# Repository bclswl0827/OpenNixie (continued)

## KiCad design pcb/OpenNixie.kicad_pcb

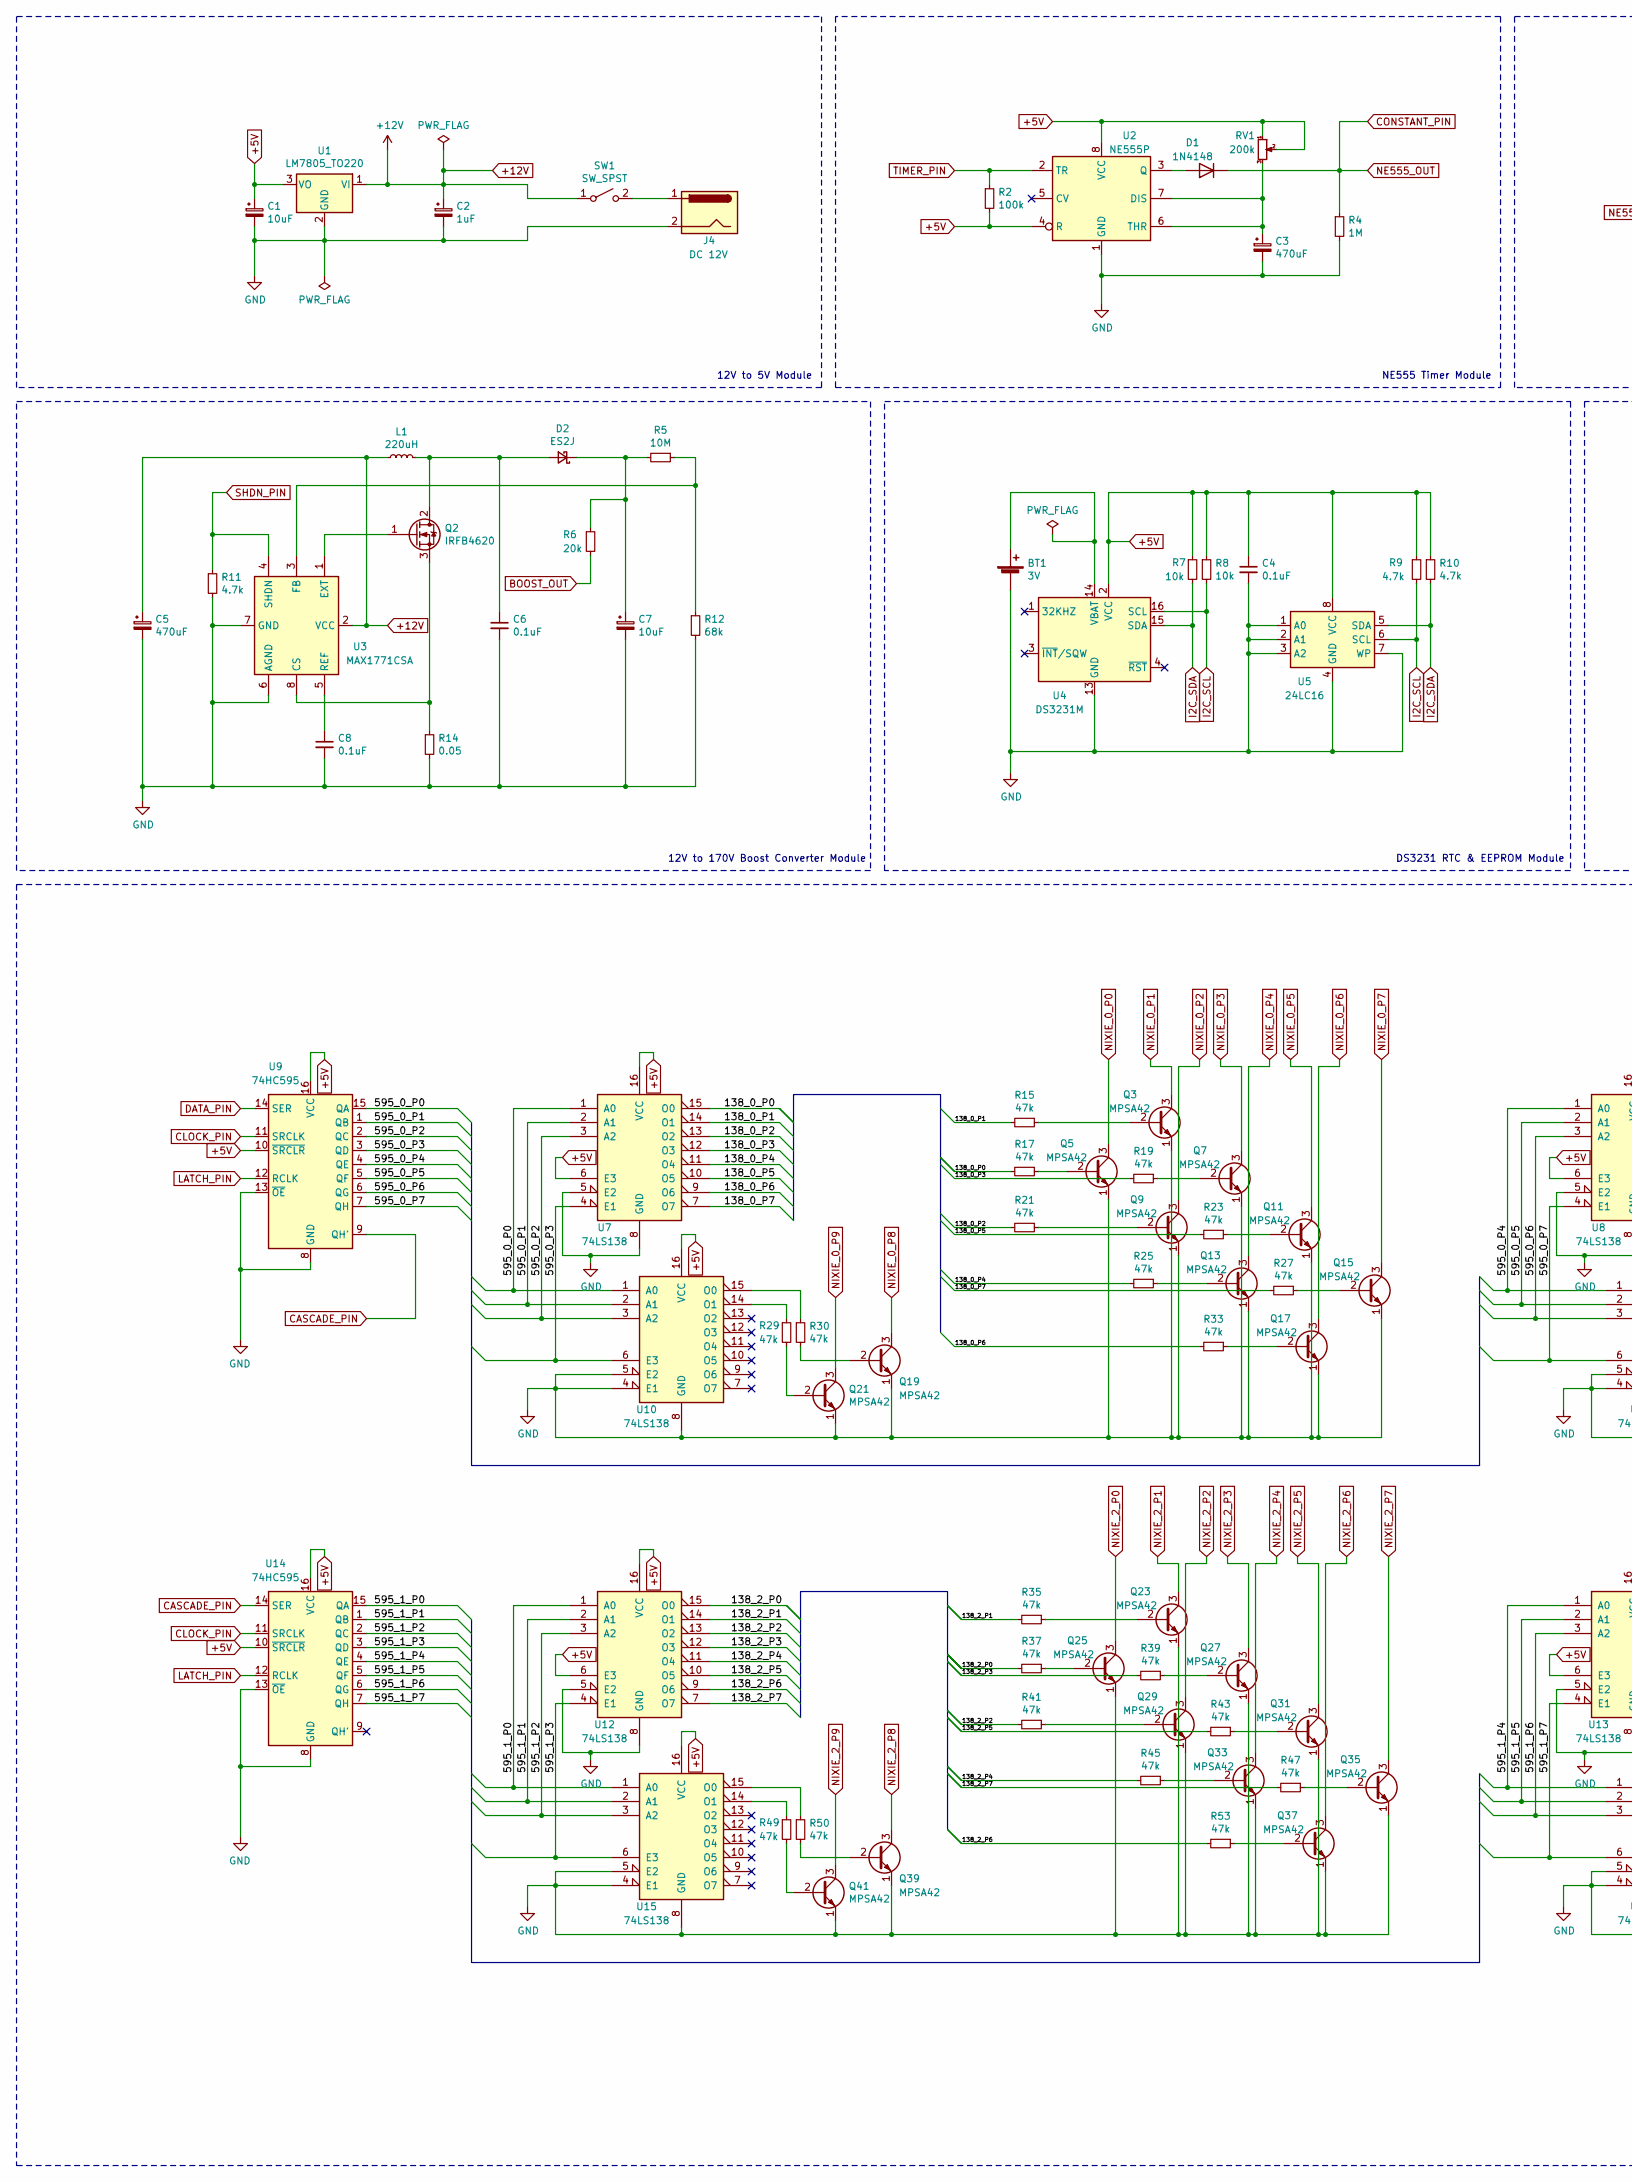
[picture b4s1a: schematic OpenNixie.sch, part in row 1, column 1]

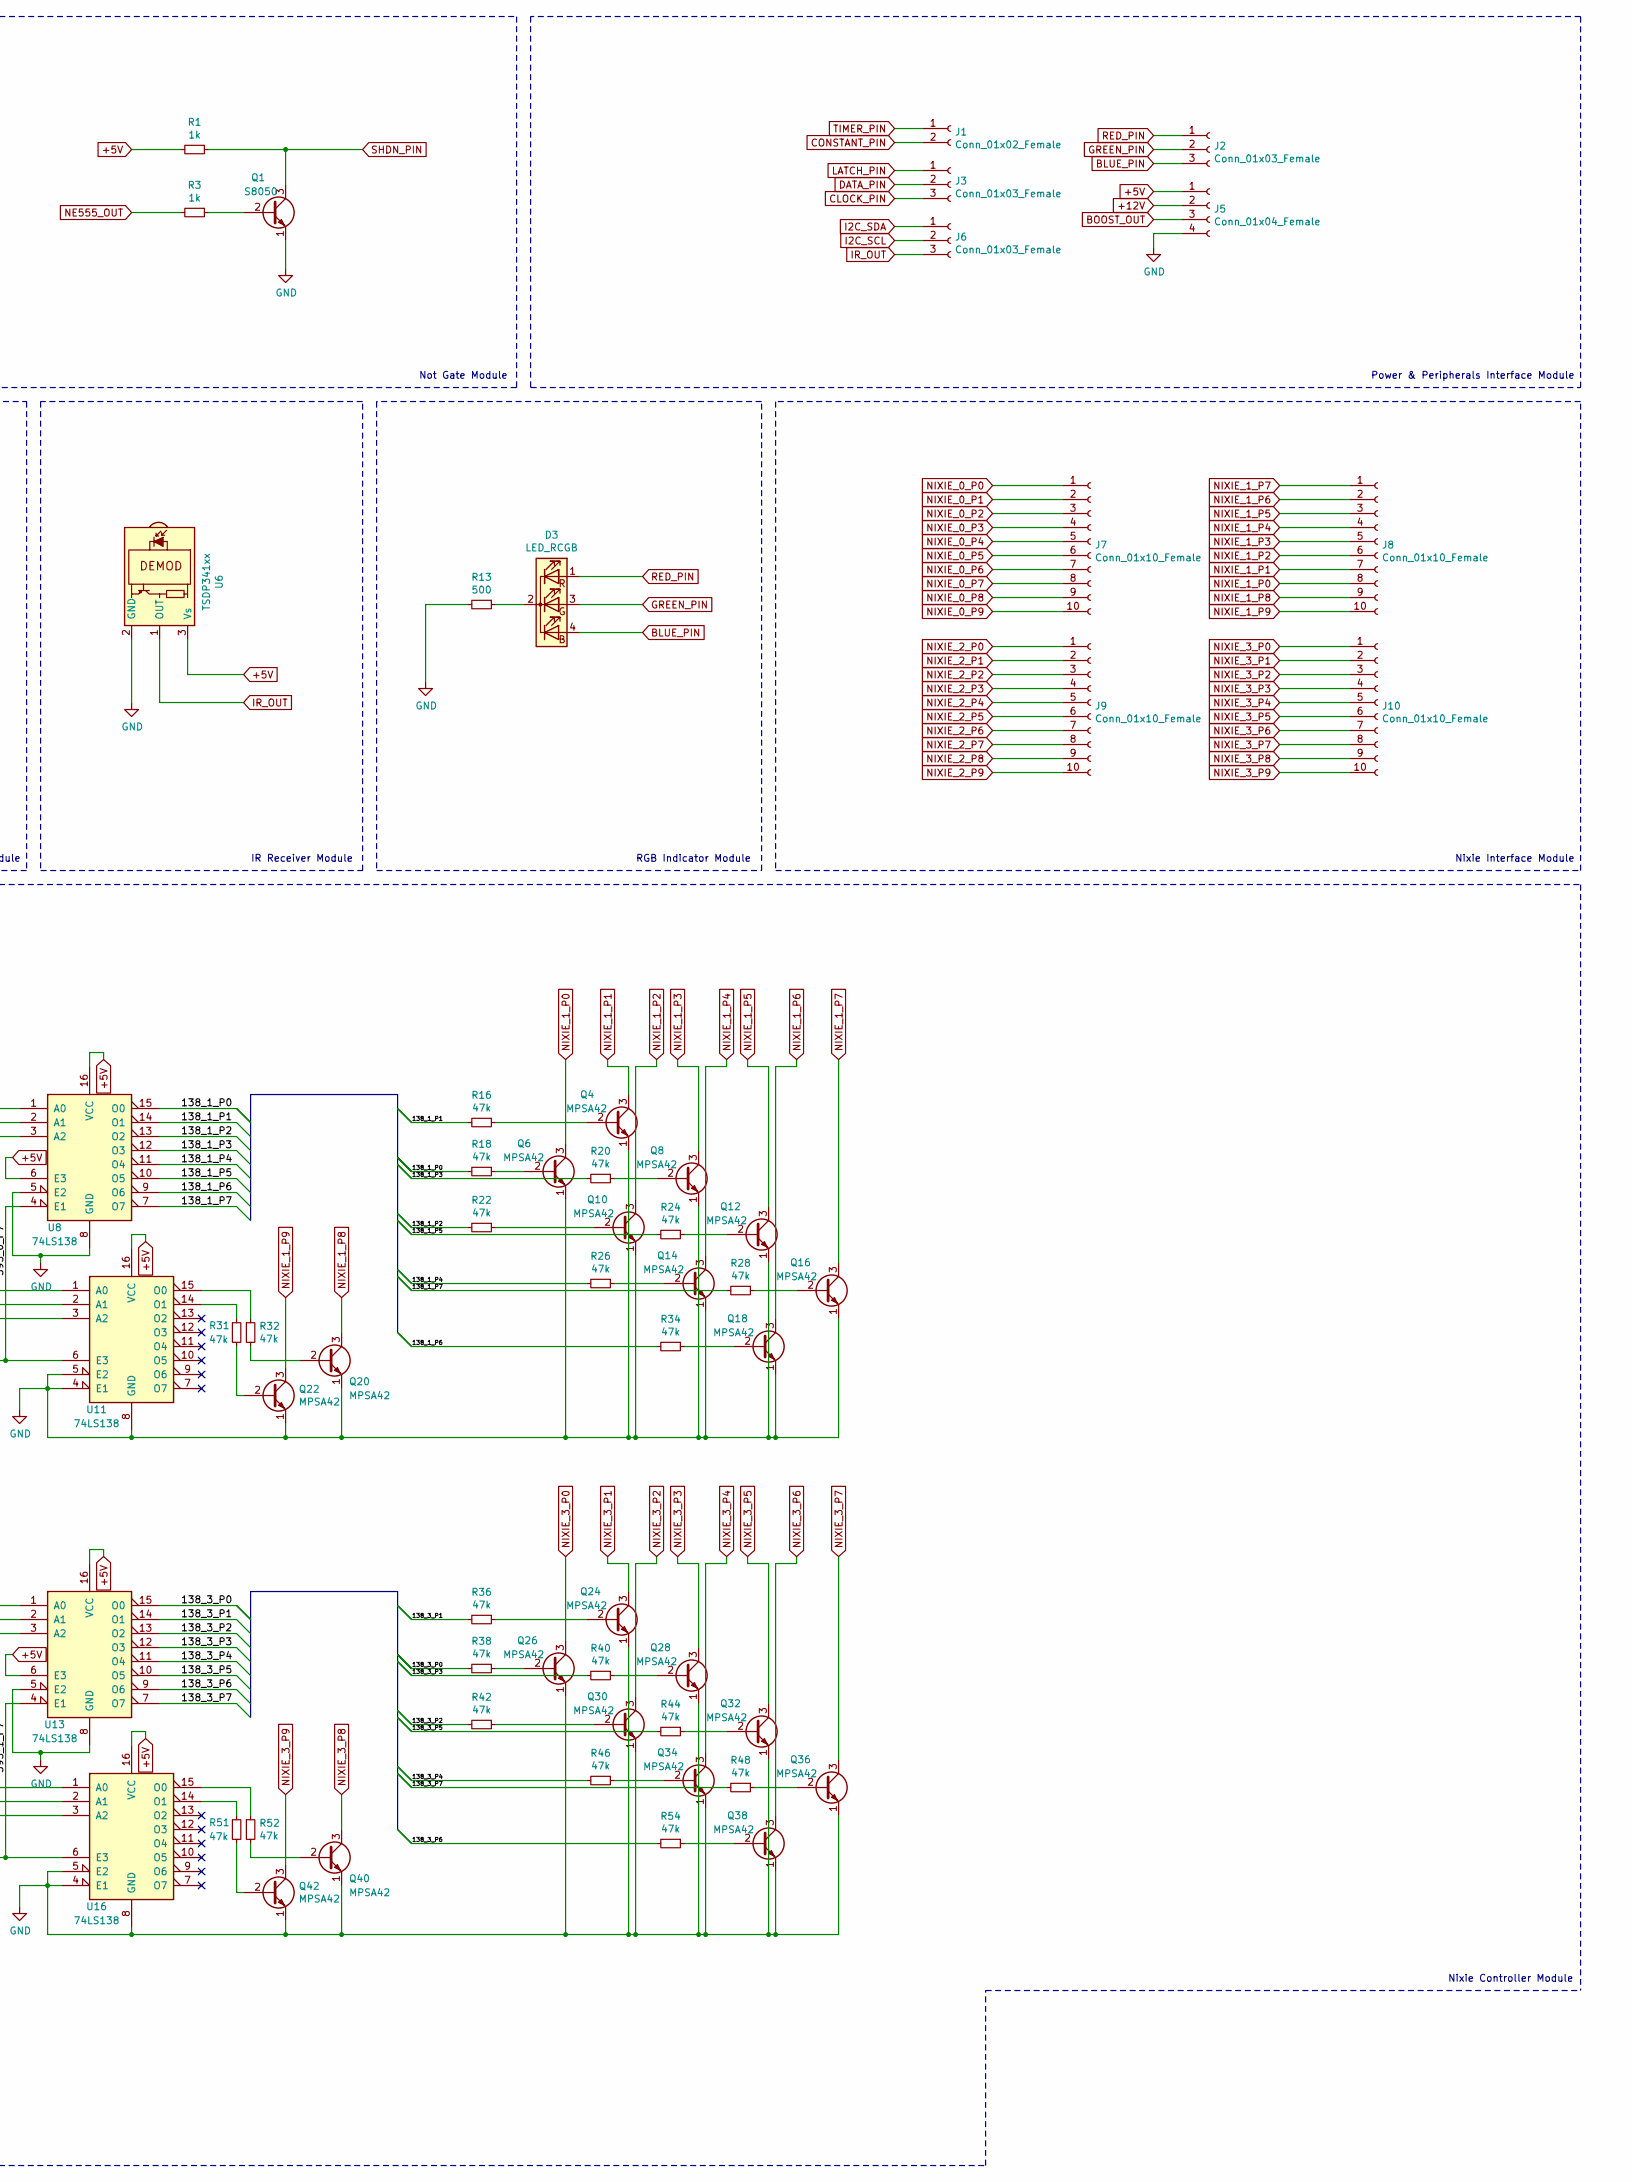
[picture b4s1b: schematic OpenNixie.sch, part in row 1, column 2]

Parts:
BT1: 3V; BatteryHolder_Keystone_1058_1x2032
C1, C7: 10uF; CP_Radial_D5.0mm_P2.50mm
C2: 1uF; CP_Radial_D5.0mm_P2.50mm
C3, C5: 470uF; CP_Radial_D8.0mm_P3.50mm
C4, C8: 0.1uF; C_Disc_D3.0mm_W2.0mm_P2.50mm
C6: 0.1uF; C_Disc_D3.0mm_W1.6mm_P2.50mm
D1: 1N4148; D_DO-35_SOD27_P7.62mm_Horizontal
D2: ES2J; D_SMA
D3: LED_RCGB; LED_D5.0mm-4_RGB
J1: Conn_01x02_Female; PinSocket_1x02_P2.54mm_Vertical
J2, J3, J6: Conn_01x03_Female; PinSocket_1x03_P2.54mm_Vertical
J4: DC 12V; BarrelJack_Horizontal
J5: Conn_01x04_Female; PinSocket_1x04_P2.54mm_Vertical
J7, J8, J9, J10: Conn_01x10_Female; PinSocket_1x10_P2.54mm_Vertical
L1: 220uH; L_Radial_D7.0mm_P3.00mm
Q1: S8050; TO-92_Inline
Q2: IRFB4620; TO-220-3_Horizontal_TabDown
Q3, Q4, Q5, Q6, Q7, Q8, Q9, Q10, Q11, Q12, Q13, Q14, Q15, Q16, Q17, Q18, Q19, Q20, Q21, Q22, Q23, Q24, Q25, Q26, Q27, Q28, Q29, Q30, Q31, Q32, Q33, Q34, Q35, Q36, Q37, Q38, Q39, Q40, Q41, Q42: MPSA42; TO-92_Inline
R1, R3: 1k; R_Axial_DIN0204_L3.6mm_D1.6mm_P7.62mm_Horizontal
R2: 100k; R_Axial_DIN0204_L3.6mm_D1.6mm_P7.62mm_Horizontal
R4: 1M; R_Axial_DIN0204_L3.6mm_D1.6mm_P7.62mm_Horizontal
R5: 10M; R_Axial_DIN0204_L3.6mm_D1.6mm_P7.62mm_Horizontal
R6: 20k; R_Axial_DIN0204_L3.6mm_D1.6mm_P7.62mm_Horizontal
R7, R8: 10k; R_Axial_DIN0204_L3.6mm_D1.6mm_P7.62mm_Horizontal
R9, R10, R11: 4.7k; R_Axial_DIN0204_L3.6mm_D1.6mm_P7.62mm_Horizontal
R12: 68k; R_Axial_DIN0204_L3.6mm_D1.6mm_P7.62mm_Horizontal
R13: 500; R_Axial_DIN0204_L3.6mm_D1.6mm_P7.62mm_Horizontal
R14: 0.05; R_Axial_DIN0207_L6.3mm_D2.5mm_P10.16mm_Horizontal
R15, R16, R17, R18, R19, R20, R21, R22, R23, R24, R25, R26, R27, R28, R29, R30, R31, R32, R33, R34, R35, R36, R37, R38, R39, R40, R41, R42, R43, R44, R45, R46, R47, R48, R49, R50, R51, R52, R53, R54: 47k; R_Axial_DIN0204_L3.6mm_D1.6mm_P7.62mm_Horizontal
RV1: 200k; Potentiometer_Vishay_T73YP_Vertical
SW1: SW_SPST; SW_DIP_SPSTx01_Slide_9.78x4.72mm_W7.62mm_P2.54mm
U1: LM7805_TO220; TO-220-3_Vertical
U2: NE555P; DIP-8_W7.62mm
U3: MAX1771CSA; SOIC-8-1EP_3.9x4.9mm_P1.27mm_EP2.29x3mm
U4: DS3231M; SOIC-16W_7.5x10.3mm_P1.27mm
U5: 24LC16; DIP-8_W7.62mm
U6: TSDP341xx; Vishay_MOLD-3Pin
U7, U8, U10, U11, U12, U13, U15, U16: 74LS138; DIP-16_W7.62mm
U9, U14: 74HC595; DIP-16_W7.62mm

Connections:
+5V: C1.1, C4.1, J5.1, R1.2, R2.2, R7.1, R8.1, R9.1, R10.1, RV1.1, RV1.2, U1.3 (VO), U2.4 (R), U2.8 (VCC), U4.2 (VCC), U5.8 (VCC), U6.3 (Vs), U7.6 (E3), U7.16 (VCC), U8.6 (E3), U8.16 (VCC), U9.10 (~SRCLR), U9.16 (VCC), U10.16 (VCC), U11.16 (VCC), U12.6 (E3), U12.16 (VCC), U13.6 (E3), U13.16 (VCC), U14.10 (~SRCLR), U14.16 (VCC), U15.16 (VCC), U16.16 (VCC)
+12V: C2.1, C5.1, J5.2, L1.1, SW1.1 (A), U1.1 (VI), U3.2 (VCC)
/138_0_P0: R17.2, U7.15 (O0)
/138_0_P1: R15.2, U7.14 (O1)
/138_0_P2: R21.2, U7.13 (O2)
/138_0_P3: R19.2, U7.12 (O3)
/138_0_P4: R25.2, U7.11 (O4)
/138_0_P5: R23.2, U7.10 (O5)
/138_0_P6: R33.2, U7.9 (O6)
/138_0_P7: R27.2, U7.7 (O7)
/138_1_P0: R18.2, U8.15 (O0)
/138_1_P1: R16.2, U8.14 (O1)
/138_1_P2: R22.2, U8.13 (O2)
/138_1_P3: R20.2, U8.12 (O3)
/138_1_P4: R26.2, U8.11 (O4)
/138_1_P5: R24.2, U8.10 (O5)
/138_1_P6: R34.2, U8.9 (O6)
/138_1_P7: R28.2, U8.7 (O7)
/138_2_P0: R37.2, U12.15 (O0)
/138_2_P1: R35.2, U12.14 (O1)
/138_2_P2: R41.2, U12.13 (O2)
/138_2_P3: R39.2, U12.12 (O3)
/138_2_P4: R45.2, U12.11 (O4)
/138_2_P5: R43.2, U12.10 (O5)
/138_2_P6: R53.2, U12.9 (O6)
/138_2_P7: R47.2, U12.7 (O7)
/138_3_P0: R38.2, U13.15 (O0)
/138_3_P1: R36.2, U13.14 (O1)
/138_3_P2: R42.2, U13.13 (O2)
/138_3_P3: R40.2, U13.12 (O3)
/138_3_P4: R46.2, U13.11 (O4)
/138_3_P5: R44.2, U13.10 (O5)
/138_3_P6: R54.2, U13.9 (O6)
/138_3_P7: R48.2, U13.7 (O7)
/595_0_P0: U7.1 (A0), U9.15 (QA), U10.1 (A0)
/595_0_P1: U7.2 (A1), U9.1 (QB), U10.2 (A1)
/595_0_P2: U7.3 (A2), U9.2 (QC), U10.3 (A2)
/595_0_P3: U7.4 (E1), U9.3 (QD), U10.6 (E3)
/595_0_P4: U8.1 (A0), U9.4 (QE), U11.1 (A0)
/595_0_P5: U8.2 (A1), U9.5 (QF), U11.2 (A1)
/595_0_P6: U8.3 (A2), U9.6 (QG), U11.3 (A2)
/595_0_P7: U8.4 (E1), U9.7 (QH), U11.6 (E3)
/595_1_P0: U12.1 (A0), U14.15 (QA), U15.1 (A0)
/595_1_P1: U12.2 (A1), U14.1 (QB), U15.2 (A1)
/595_1_P2: U12.3 (A2), U14.2 (QC), U15.3 (A2)
/595_1_P3: U12.4 (E1), U14.3 (QD), U15.6 (E3)
/595_1_P4: U13.1 (A0), U14.4 (QE), U16.1 (A0)
/595_1_P5: U13.2 (A1), U14.5 (QF), U16.2 (A1)
/595_1_P6: U13.3 (A2), U14.6 (QG), U16.3 (A2)
/595_1_P7: U13.4 (E1), U14.7 (QH), U16.6 (E3)
BLUE_PIN: D3.4 (BA), J2.3
BOOST_OUT: J5.3, R6.2
CASCADE_PIN: U9.9 (QH'), U14.14 (SER)
CLOCK_PIN: J3.3, U9.11 (SRCLK), U14.11 (SRCLK)
CONSTANT_PIN: D1.1 (K), J1.2, R3.2, R4.1
DATA_PIN: J3.2, U9.14 (SER)
GND: BT1.2 (-), C1.2, C2.2, C3.2, C4.2, C5.2, C6.2, C7.2, C8.2, J4.2, J5.4, Q1.1 (E), Q3.1 (E), Q4.1 (E), Q5.1 (E), Q6.1 (E), Q7.1 (E), Q8.1 (E), Q9.1 (E), Q10.1 (E), Q11.1 (E), Q12.1 (E), Q13.1 (E), Q14.1 (E), Q15.1 (E), Q16.1 (E), Q17.1 (E), Q18.1 (E), Q19.1 (E), Q20.1 (E), Q21.1 (E), Q22.1 (E), Q23.1 (E), Q24.1 (E), Q25.1 (E), Q26.1 (E), Q27.1 (E), Q28.1 (E), Q29.1 (E), Q30.1 (E), Q31.1 (E), Q32.1 (E), Q33.1 (E), Q34.1 (E), Q35.1 (E), Q36.1 (E), Q37.1 (E), Q38.1 (E), Q39.1 (E), Q40.1 (E), Q41.1 (E), Q42.1 (E), R4.2, R11.2, R12.2, R13.2, R14.2, U1.2 (GND), U2.1 (GND), U3.6 (AGND), U3.7 (GND), U4.5 (GND), U4.6 (GND), U4.7 (GND), U4.8 (GND), U4.9 (GND), U4.10 (GND), U4.11 (GND), U4.12 (GND), U4.13 (GND), U5.1 (A0), U5.2 (A1), U5.3 (A2), U5.4 (GND), U5.7 (WP), U6.2 (GND), U7.5 (E2), U7.8 (GND), U8.5 (E2), U8.8 (GND), U9.8 (GND), U9.13 (~OE), U10.4 (E1), U10.5 (E2), U10.8 (GND), U11.4 (E1), U11.5 (E2), U11.8 (GND), U12.5 (E2), U12.8 (GND), U13.5 (E2), U13.8 (GND), U14.8 (GND), U14.13 (~OE), U15.4 (E1), U15.5 (E2), U15.8 (GND), U16.4 (E1), U16.5 (E2), U16.8 (GND)
GREEN_PIN: D3.3 (GA), J2.2
I2C_SCL: J6.2, R8.2, R9.2, U4.16 (SCL), U5.6 (SCL)
I2C_SDA: J6.1, R7.2, R10.2, U4.15 (SDA), U5.5 (SDA)
IR_OUT: J6.3, U6.1 (OUT)
LATCH_PIN: J3.1, U9.12 (RCLK), U14.12 (RCLK)
NIXIE_0_P0: J7.1, Q5.3 (C)
NIXIE_0_P1: J7.2, Q3.3 (C)
NIXIE_0_P2: J7.3, Q9.3 (C)
NIXIE_0_P3: J7.4, Q7.3 (C)
NIXIE_0_P4: J7.5, Q13.3 (C)
NIXIE_0_P5: J7.6, Q11.3 (C)
NIXIE_0_P6: J7.7, Q17.3 (C)
NIXIE_0_P7: J7.8, Q15.3 (C)
NIXIE_0_P8: J7.9, Q19.3 (C)
NIXIE_0_P9: J7.10, Q21.3 (C)
NIXIE_1_P0: J8.8, Q6.3 (C)
NIXIE_1_P1: J8.7, Q4.3 (C)
NIXIE_1_P2: J8.6, Q10.3 (C)
NIXIE_1_P3: J8.5, Q8.3 (C)
NIXIE_1_P4: J8.4, Q14.3 (C)
NIXIE_1_P5: J8.3, Q12.3 (C)
NIXIE_1_P6: J8.2, Q18.3 (C)
NIXIE_1_P7: J8.1, Q16.3 (C)
NIXIE_1_P8: J8.9, Q20.3 (C)
NIXIE_1_P9: J8.10, Q22.3 (C)
NIXIE_2_P0: J9.1, Q25.3 (C)
NIXIE_2_P1: J9.2, Q23.3 (C)
NIXIE_2_P2: J9.3, Q29.3 (C)
NIXIE_2_P3: J9.4, Q27.3 (C)
NIXIE_2_P4: J9.5, Q33.3 (C)
NIXIE_2_P5: J9.6, Q31.3 (C)
NIXIE_2_P6: J9.7, Q37.3 (C)
NIXIE_2_P7: J9.8, Q35.3 (C)
NIXIE_2_P8: J9.9, Q39.3 (C)
NIXIE_2_P9: J9.10, Q41.3 (C)
NIXIE_3_P0: J10.1, Q26.3 (C)
NIXIE_3_P1: J10.2, Q24.3 (C)
NIXIE_3_P2: J10.3, Q30.3 (C)
NIXIE_3_P3: J10.4, Q28.3 (C)
NIXIE_3_P4: J10.5, Q34.3 (C)
NIXIE_3_P5: J10.6, Q32.3 (C)
NIXIE_3_P6: J10.7, Q38.3 (C)
NIXIE_3_P7: J10.8, Q36.3 (C)
NIXIE_3_P8: J10.9, Q40.3 (C)
NIXIE_3_P9: J10.10, Q42.3 (C)
unnamed: BT1.1 (+), U4.14 (VBAT)
unnamed: C3.1, RV1.3, U2.6 (THR), U2.7 (DIS)
unnamed: C6.1, D2.2 (A), L1.2, Q2.2 (D)
unnamed: C7.1, D2.1 (K), R5.2, R6.1
unnamed: C8.1, U3.5 (REF)
unnamed: D1.2 (A), U2.3 (Q)
unnamed: D3.2 (K), R13.1
unnamed: J4.1, SW1.2 (B)
unnamed: Q1.2 (B), R3.1
unnamed: Q2.1 (G), U3.1 (EXT)
unnamed: Q2.3 (S), R14.1, U3.8 (CS)
unnamed: Q3.2 (B), R15.1
unnamed: Q4.2 (B), R16.1
unnamed: Q5.2 (B), R17.1
unnamed: Q6.2 (B), R18.1
unnamed: Q7.2 (B), R19.1
unnamed: Q8.2 (B), R20.1
unnamed: Q9.2 (B), R21.1
unnamed: Q10.2 (B), R22.1
unnamed: Q11.2 (B), R23.1
unnamed: Q12.2 (B), R24.1
unnamed: Q13.2 (B), R25.1
unnamed: Q14.2 (B), R26.1
unnamed: Q15.2 (B), R27.1
unnamed: Q16.2 (B), R28.1
unnamed: Q17.2 (B), R33.1
unnamed: Q18.2 (B), R34.1
unnamed: Q19.2 (B), R30.2
unnamed: Q20.2 (B), R32.2
unnamed: Q21.2 (B), R29.2
unnamed: Q22.2 (B), R31.2
unnamed: Q23.2 (B), R35.1
unnamed: Q24.2 (B), R36.1
unnamed: Q25.2 (B), R37.1
unnamed: Q26.2 (B), R38.1
unnamed: Q27.2 (B), R39.1
unnamed: Q28.2 (B), R40.1
unnamed: Q29.2 (B), R41.1
unnamed: Q30.2 (B), R42.1
unnamed: Q31.2 (B), R43.1
unnamed: Q32.2 (B), R44.1
unnamed: Q33.2 (B), R45.1
unnamed: Q34.2 (B), R46.1
unnamed: Q35.2 (B), R47.1
unnamed: Q36.2 (B), R48.1
unnamed: Q37.2 (B), R53.1
unnamed: Q38.2 (B), R54.1
unnamed: Q39.2 (B), R50.2
unnamed: Q40.2 (B), R52.2
unnamed: Q41.2 (B), R49.2
unnamed: Q42.2 (B), R51.2
unnamed: R5.1, R12.1, U3.3 (FB)
unnamed: R29.1, U10.14 (O1)
unnamed: R30.1, U10.15 (O0)
unnamed: R31.1, U11.14 (O1)
unnamed: R32.1, U11.15 (O0)
unnamed: R49.1, U15.14 (O1)
unnamed: R50.1, U15.15 (O0)
unnamed: R51.1, U16.14 (O1)
unnamed: R52.1, U16.15 (O0)
RED_PIN: D3.1 (RA), J2.1
SHDN_PIN: Q1.3 (C), R1.1, R11.1, U3.4 (SHDN)
TIMER_PIN: J1.1, R2.1, U2.2 (TR)

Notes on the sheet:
NE555 Timer Module
Not Gate Module
DS3231 RTC & EEPROM Module
RGB Indicator Module
IR Receiver Module
12V to 170V Boost Converter Module
Power & Peripherals Interface Module
Nixie Interface Module
Nixie Controller Module
12V to 5V Module

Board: 2 copper layers, 137 parts (0 on the bottom side), 165 nets, no tracks yet.

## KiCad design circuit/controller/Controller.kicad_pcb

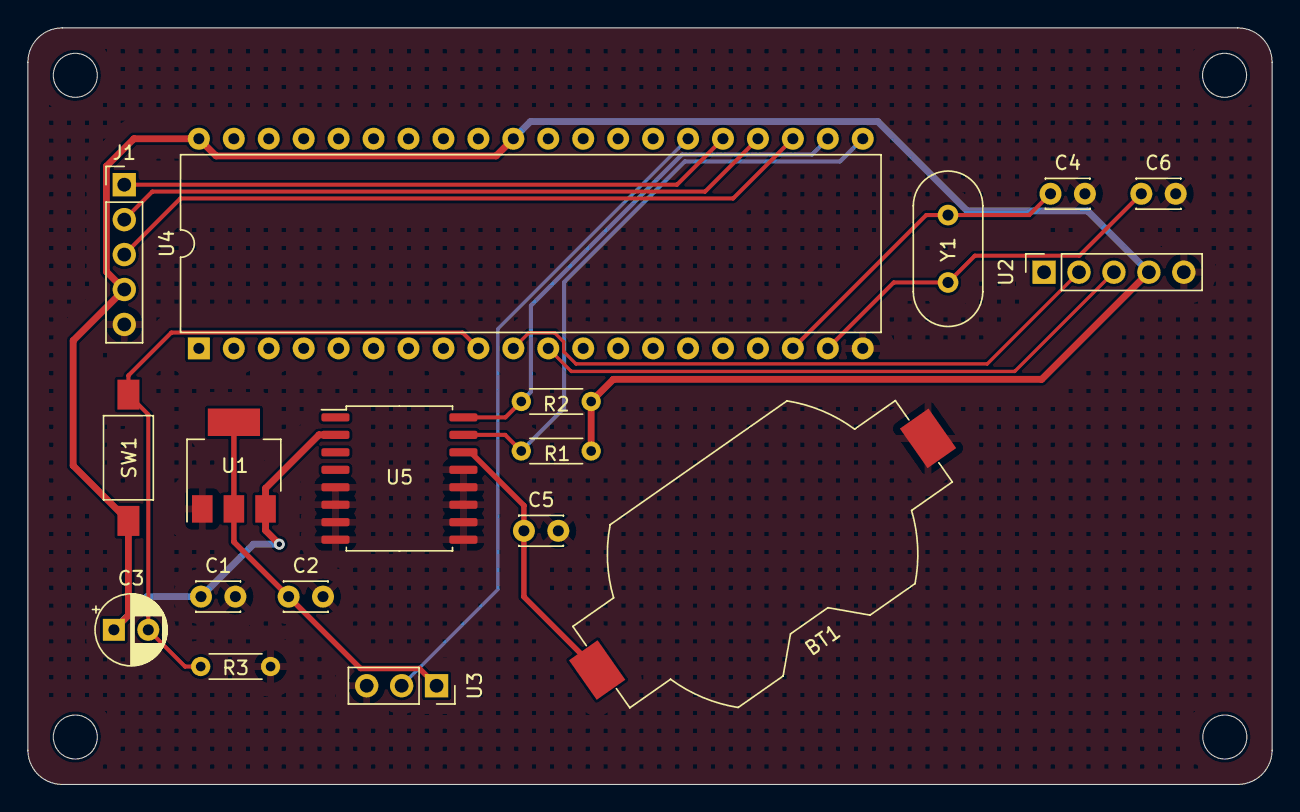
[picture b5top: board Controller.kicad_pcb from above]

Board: 2 copper layers, 90.5 x 55.0 mm, 22 parts (0 on the bottom side), 15 nets.

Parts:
BT1: 3V; BatteryHolder_Keystone_1058_1x2032
C1, C2, C5: 0.1uF; C_Disc_D3.0mm_W2.0mm_P2.50mm
C3: 10uF; CP_Radial_D5.0mm_P2.50mm
C4, C6: 20pF; C_Disc_D3.0mm_W2.0mm_P2.50mm
H1, H2, H3, H4: MountingHole; MountingHole_3.2mm_M3
J1: Conn_01x05; PinHeader_1x05_P2.54mm_Vertical
R1, R2, R3: 10k; R_Axial_DIN0204_L3.6mm_D1.6mm_P5.08mm_Horizontal
SW1: SW_Push; SW_SPST_FSMSM
U1: AMS1117-3.3; SOT-223-3_TabPin2
U2: JDY-34; PinSocket_1x05_P2.54mm_Vertical
U3: AM312; PinSocket_1x03_P2.54mm_Vertical
U4: AT89C52; DIP-40_W15.24mm
U5: DS3231M; SOIC-16W_7.5x10.3mm_P1.27mm
Y1: 11.0592MHz; Crystal_HC18-U_Vertical

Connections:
+5V: C1.1, C3.1, J1.4, R1.2, R2.2, SW1.1, U1.3 (VI), U2.4 (VCC), U4.31 (~EA/VPP), U4.40 (VCC), U5.2 (VCC)
/+3.3V: C2.1, U1.2 (VO), U3.1 (VCC)
/BLE_RXD: U2.3 (RXD), U4.11 (P3.1(TXD))
/BLE_TXD: U2.2 (TXD), U4.10 (P3.0(RXD))
/I2C_SCL: R2.1, U4.22 (P2.1), U5.16 (SCL)
/I2C_SDA: R1.1, U4.21 (P2.0), U5.15 (SDA)
/PIR: U3.2 (OUT), U4.26 (P2.5)
/SR_CLK: J1.3, U4.23 (P2.2)
/SR_DAT: J1.2, U4.24 (P2.3)
/SR_LCH: J1.1, U4.25 (P2.4)
/VBAT: BT1.1 (+), C5.1, U5.14 (VBAT)
GND: BT1.2 (-), C1.2, C2.2, C4.2, C5.2, C6.2, J1.5, R3.2, U1.1 (GND), U2.5 (GND), U3.3 (GND), U4.20 (GND), U5.5 (GND), U5.6 (GND), U5.7 (GND), U5.8 (GND), U5.9 (GND), U5.10 (GND), U5.11 (GND), U5.12 (GND), U5.13 (GND)
unnamed: C4.1, U4.18 (X1), Y1.2
unnamed: C6.1, U4.19 (X2), Y1.1
unnamed: C3.2, R3.1, SW1.2, U4.9 (~RESET)

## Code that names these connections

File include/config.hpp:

#pragma once

// 调试模式开关
#define DEBUG_FLAG 0
// 调试模式波特率
#define DEBUG_BAUD 9600

// 扫描速度
#define SCAN_SPEED 28
// 画面扫描持续时间
#define SCAN_TIME 5000
// 按钮防抖动时间
#define DEBOUNCE_DELAY 1000
// 对时按钮，须 D2 或 D3
#define TIME_PIN D2

// RTC 模块型号
#define RTC_MODEL 2
// RTC 模块地址
#define RTC_ADDR 0x68
// RTC 模块 SDA
#define RTC_SDA SDA  // PIN_A4
// RTC 模块 SCL
#define RTC_SCL SCL  // PIN_A5

// 蓝牙串口波特率
#define BLUETH_BAUD 9600
// 蓝牙超时时间
#define BLUETH_TIMEOUT 500
// 对时重试次数
#define BLUETH_RETRY 100
// 蓝牙串口 RX
#define BLUETH_RX A2
// 蓝牙串口 TX
#define BLUETH_TX A3

// 红色指示灯
#define RGB_RED D7
// 绿色指示灯
#define RGB_GRN D8
// 蓝色指示灯
#define RGB_BLE D9

// 移位寄存器 ST_CP（Latch）
#define SR_LATCH D10
// 移位寄存器 DS（Data）
#define SR_DATA D11
// 移位寄存器 SH_CP（Clock）
#define SR_CLOCK D12

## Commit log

2023-01-20 Source uploaded
2023-01-23 Schematic updated
2023-01-24 Lint & Schematic update
2023-01-25 Schematic update
2023-01-26 PCB layout updated
2023-01-31 PCB Layout for QS27-1
2023-01-31 Fix nixie pin assignment
2023-02-07 Fix layout errors
2023-02-08 Change footprint
2023-02-08 Add schematic & PCB for IN12
2023-02-08 Add uRTCLib as submodule
2023-02-08 Update submodule repo url
2023-02-08 Fixes
2023-02-08 Updates on resistor values
2023-02-15 Refactoring with 4-bit dynamic scan
2023-02-19 Fix typo on nixie segment
2023-02-20 Update on PCB
2023-02-28 Ver 3.0
2023-03-26 Update resistor value
2023-06-28 PCB updated
2023-07-03 Some fixes
2023-07-03 Fix layout
2023-07-25 Refactored with a better solution
2023-07-25 Remove Makefile
2023-07-25 Update circuit path
2023-07-25 Clean circuit files
2023-07-25 Add Python demo
2023-07-25 Add 1 second when aligning
2023-07-26 Hide symbol when showing date
2023-07-26 Fix typo
2023-07-26 Add React version
2023-07-26 Add workflow
2023-07-26 Fix dist folder
2023-07-26 Deploying to gh-pages from @ c7913906af15bb490f921547d29bfd6a45348db5 🚀
2023-07-26 Fix homepage URL
2023-07-26 Deploying to gh-pages from @ 6d0eb614684e73226bbabe08f9d86fd91f561d1f 🚀
2023-07-26 Add delay on each command
2023-07-26 Deploying to gh-pages from @ c0be39b65456eea5d94f96383c5ba0f2678e1b1b 🚀
2023-07-26 More optimization
2023-07-26 Deploying to gh-pages from @ b9a8ef19837c47a5379396058cfb756671836ea9 🚀
2023-07-26 Update gerbers
2023-07-26 Some clean work
2023-08-22 Deploying to gh-pages from @ 1e98d6159a842d8c175e0f8d69330ddfa7113ad4 🚀
2023-08-22 Some integration works
2023-08-22 Fix flash command
2023-08-23 Rename IN12 to IN-12
2023-08-23 Use Hex
2023-09-15 Add support for QS-30
2023-09-15 Deploying to gh-pages from @ d2489a0597a2c7b491a188ff7196767f9bca0416 🚀
2023-09-15 Create schematic pdf
2023-09-15 Update schematics
2023-09-15 Fix QS-30 layout
2023-09-20 Firmware update
2023-09-20 Deploying to gh-pages from @ a565dfb684b72e98ed4a968903768521d891ff1a 🚀
2023-09-30 Move bluetooth to bottom
2023-10-27 Fix silkscreen
2023-10-27 Deploying to gh-pages from @ 0f6724eeeb8146dbcd59889a6608df17bb517df2 🚀
2023-10-27 Add panel sketch
2023-10-27 Update panel
2023-10-28 Update panels
2023-10-28 Update panel size
2023-11-01 Fix screw hole size
2023-11-01 Leave option to disable protection
2024-01-01 Update README with instructions
2024-01-01 Deploying to gh-pages from @ a0f772604d39717bd1859388522ca916cf1ea15b 🚀
2024-04-09 Deploying to gh-pages from @ a2e22a8418390938fca0f19d855f88d841adaf91 🚀
